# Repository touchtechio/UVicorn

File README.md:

SLIDES on 
[Google Slides](https://docs.google.com/presentation/d/1qJo-Hg3JritGdWxLVQg1Fd6QkeQzpe9MSCtlQi5ZKv8/edit?usp=sharing)

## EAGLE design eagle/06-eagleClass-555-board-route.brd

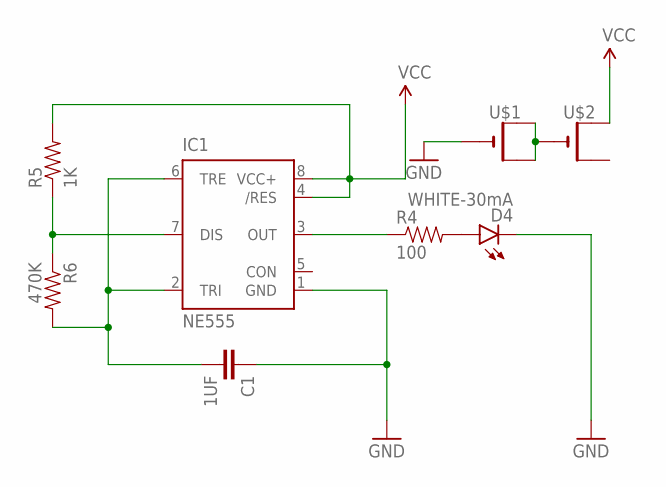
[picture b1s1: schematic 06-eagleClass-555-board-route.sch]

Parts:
C1: 1UF; AXIAL-5MM
D4: WHITE-30mA; LED5MM
IC1: NE555; DIL-08
R4: 100; AXIAL-0.3EZ
R5: 1K; AXIAL-0.3EZ
R6: 470K; AXIAL-0.3EZ
U$1, U$2: CR2032THM; CR2032-THRU

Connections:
DISCHARGE: IC1.7 (DIS), R5.P$1 (1), R6.P$1 (1)
GND: C1.P$1 (1), D4.K (C), IC1.1 (GND), U$1.-
unnamed: D4.A, R4.P$2 (2)
unnamed: U$1.+1 (+), U$1.+2 (+1), U$2.-
OUT: IC1.3 (OUT), R4.P$1 (1)
THRESHOLD: C1.P$2 (2), IC1.6 (TRE), R6.P$2 (2)
VCC: IC1.4 (/RES), IC1.8 (VCC+), R5.P$2 (2), U$2.+1 (+)

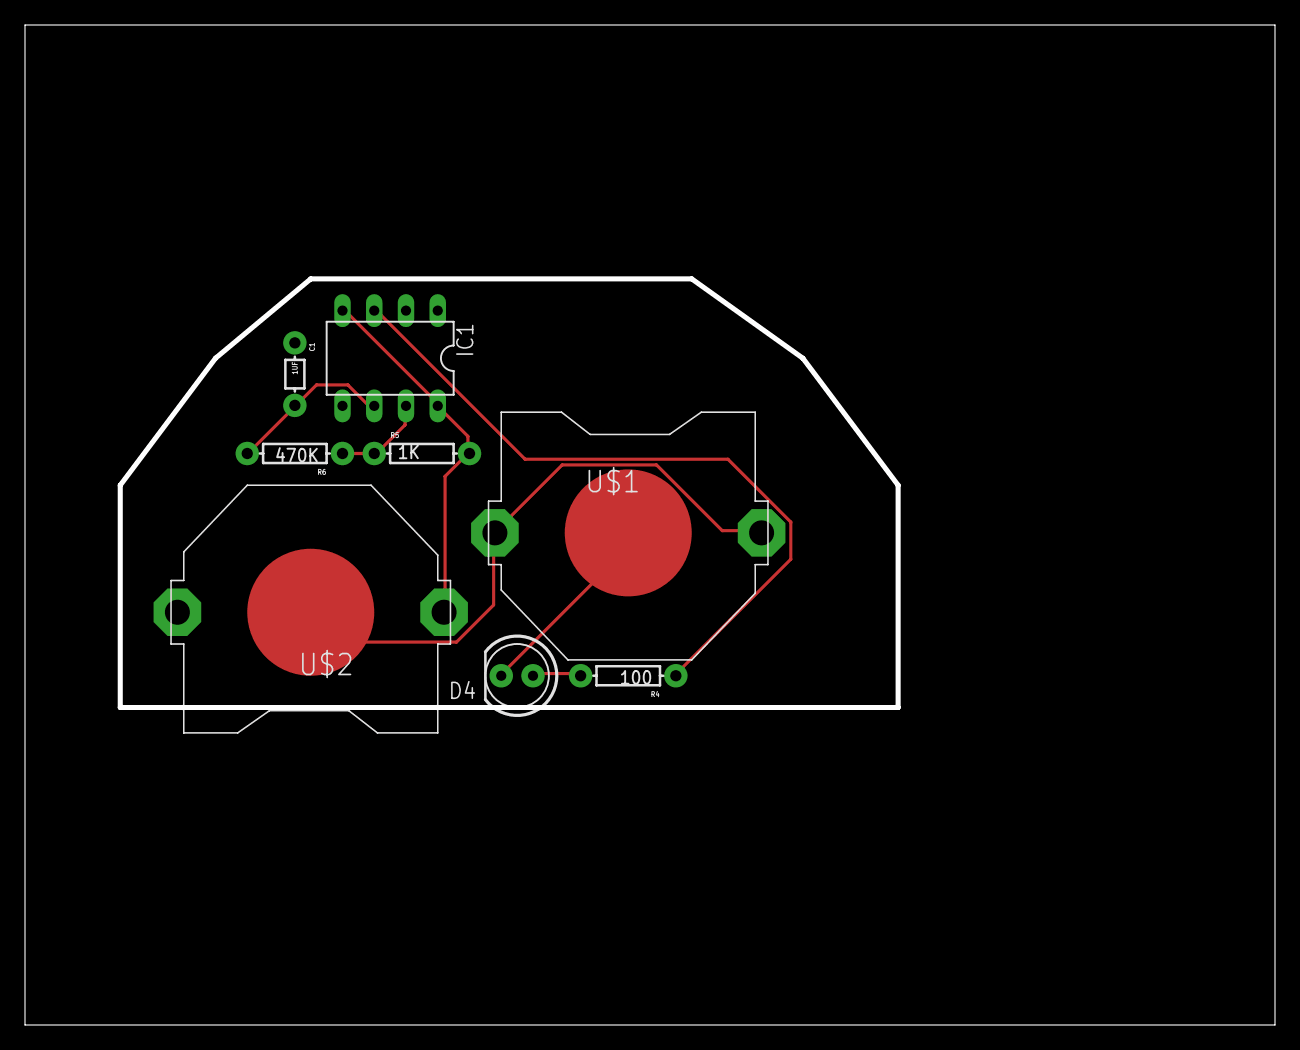
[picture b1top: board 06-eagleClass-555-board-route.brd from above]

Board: 2 copper layers, 99.6 x 79.6 mm, 8 parts (0 on the bottom side), 7 nets.

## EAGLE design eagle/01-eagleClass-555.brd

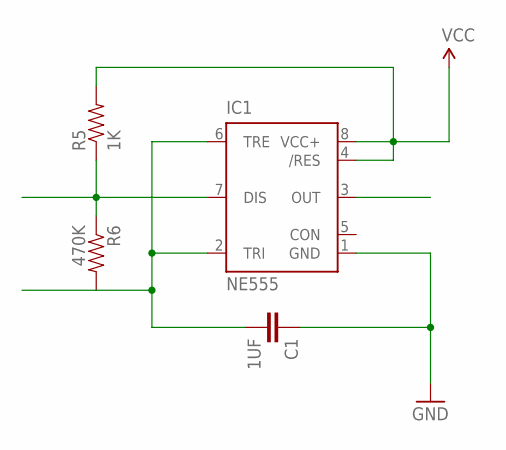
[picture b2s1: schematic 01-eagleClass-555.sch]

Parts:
C1: 1UF; AXIAL-5MM
IC1: NE555; DIL-08
R5: 1K; AXIAL-0.3EZ
R6: 470K; AXIAL-0.3EZ

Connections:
DISCHARGE: IC1.7 (DIS), R5.P$1 (1), R6.P$1 (1)
GND: C1.P$1 (1), IC1.1 (GND)
OUT: IC1.3 (OUT)
THRESHOLD: C1.P$2 (2), IC1.2 (TRI), IC1.6 (TRE), R6.P$2 (2)
VCC: IC1.4 (/RES), IC1.8 (VCC+), R5.P$2 (2)

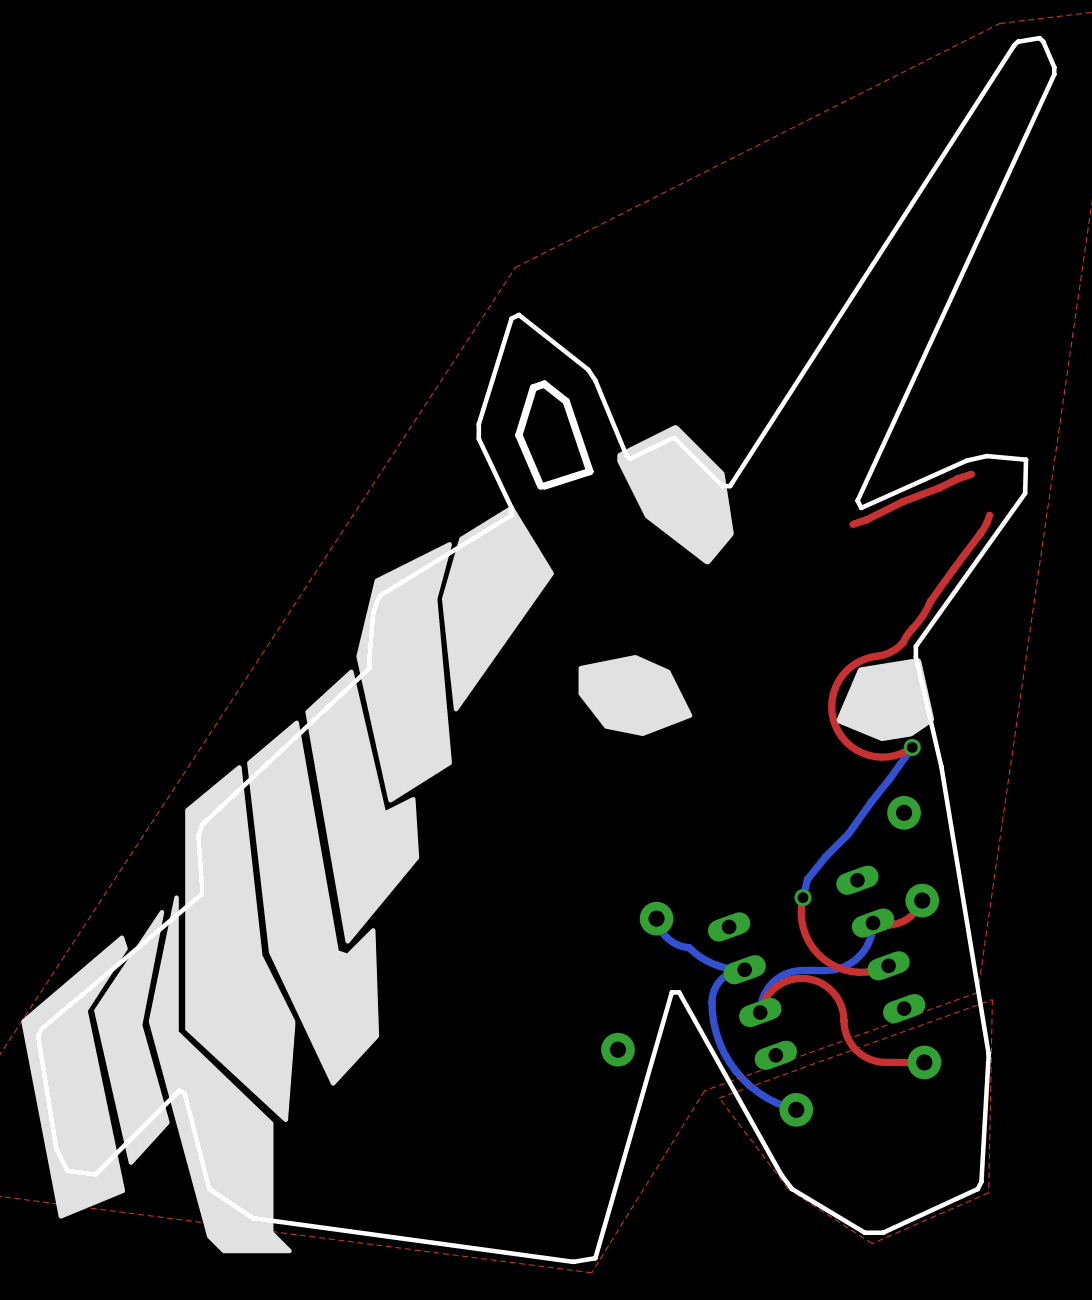
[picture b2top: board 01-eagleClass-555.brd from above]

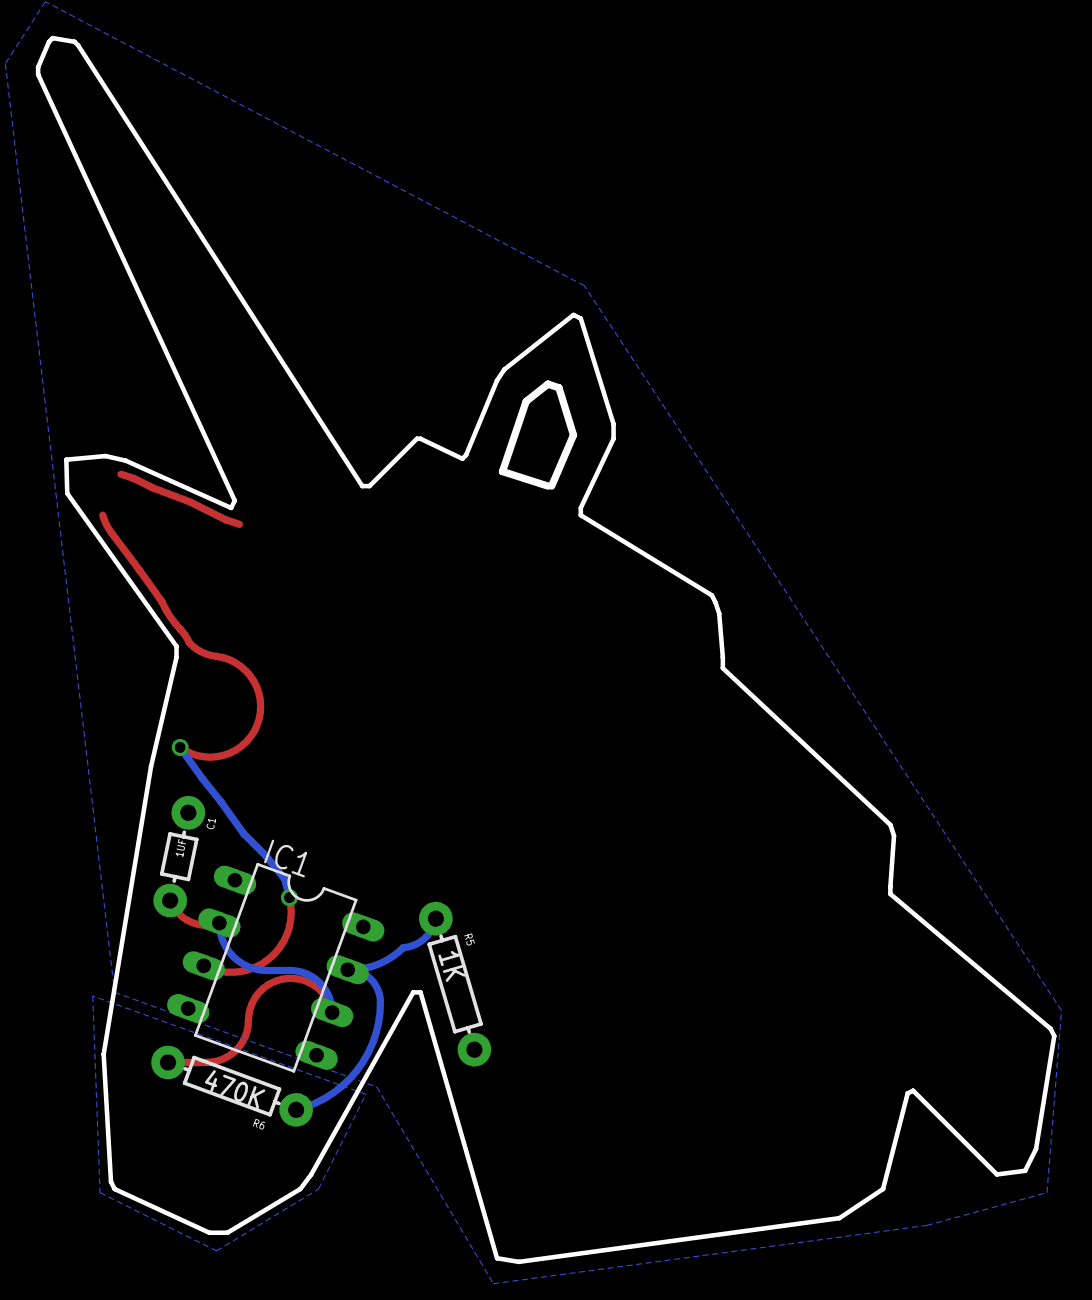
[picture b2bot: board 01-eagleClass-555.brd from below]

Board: 2 copper layers, 56.5 x 68.1 mm, 4 parts (4 on the bottom side), 4 nets.

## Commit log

2017-09-05 adding notes
2017-09-05 added presentation
2017-10-15 adding fix for threshold
2017-12-05 adding kit build documentation
2017-12-05 adding bom

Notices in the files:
parts and their libraries:
SparkFun-Resistors: Licensing: Creative Commons ShareAlike 4.0 International - https://creativecommons.org/licenses/by-sa/4.0
